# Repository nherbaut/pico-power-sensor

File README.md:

# PicoPower hand-soldered prototype

Two prototype boards for measuring voltage, current, power and energy consumed by a Raspberry Pi during AI tasks. This is the **proto branch**, with its own hand-solderable design and project history.

The interposer carries bench-supply protection and a 5 mΩ shunt. A separately USB-powered Pico carrier reads the INA228 monitor, logs measurements to microSD and drives programmable indicators.

## Current documentation

- [Requirements](docs/requirements.md) and [architecture](docs/architecture.md)
- [Bill of materials](hardware/bom.csv) and [purchase list](hardware/purchase-bom.csv)
- [Release checklist](hardware/release-checklist.csv)
- [Interposer layout](docs/interposer-layout.md) and [carrier layout](docs/carrier-layout.md)
- [Assembly and circuit explanation](docs/how-it-works.md)
- [Project handoff](HANDOFF.md) and [working instructions](AGENTS.md)

The hardware is **not released for fabrication or connection to a Pi**. Calculated values and automated checks are not bench measurements. The [2026-11-02 BOM review](docs/bom-audit-2026-11-02.md) records procurement gaps and package minimums. A [32 GB measurement-storage card](docs/measurement-storage-card.md) has been selected for prototype qualification. No parts have been purchased, as confirmed by the owner.

## Website

GitHub Pages publishes this branch. The workflow always checks out `proto`, including manual runs. Documentation and CSV tables are generated from this branch's source files; linked design files and evidence are available as downloads.

Run `make site-check BASE_URL=https://nherbaut.github.io/pico-power-sensor/` to build the site and check internal links. Hugo is required. Run `make site-serve` for a local preview.

## Hardware editing

Follow the regeneration instructions in [HANDOFF.md](HANDOFF.md). Hardware generators live in `hardware/kicad/`; the website build never regenerates or changes the CAD.

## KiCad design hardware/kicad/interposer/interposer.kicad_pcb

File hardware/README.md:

# Hardware

Start with [understanding the two boards](../docs/pcb-guide.md) for a plain-language explanation of the components, assembly and remaining work.

The [BOM](bom.csv) represents a proposed instrument, not a purchase record. [Procurement](procurement.csv) and [inventory](inventory.csv) start empty. Sources and review obligations are recorded with each component.

The first instrument combines the [custom interposer](pcb/interposer/README.md) and a Pico 2 W on the [carrier](pcb/carrier/README.md). The carrier adds five GPIO-controlled indicators, a JST-XH interposer connection and a microSD slot with its own USB-fed regulator. The Korad U202 supplies the DUT at the planned 5.1 V setting through a direct DC path. The card regulator belongs to the separately powered instrument, outside DUT measurements.

The replaceable fuse and shunt are mounted on the interposer. Current is sensed with a dedicated Kelvin pair. An upstream electronic switch disconnects incorrectly connected or excessive input voltage; it does not regulate output voltage. Its low-resistance power path still introduces a small voltage drop that must be checked under load.

The [optional BOM](optional-bom.csv) contains shared bench equipment. Calibration equipment is not part of the finished instrument.

Read the [current review findings and printable mock-ups](review/README.md), [passive component proposals](passive-proposals.csv) and [release checklist](release-checklist.csv). The [release procedure](../docs/release.md) separates prototype fabrication from assembled-board validation before Pi connection. Both gates remain blocked.

Current prototype work: [design review](../docs/design-review.md), [assembly sourcing](../docs/assembly-sourcing.md) and [fablab validation](../docs/fablab-validation.md).

The [electronic protection study](../docs/electronic-protection.md) compares fuse replacement and a copper alternative. Main CAD retains its cartridge design until the new control circuitry is qualified.

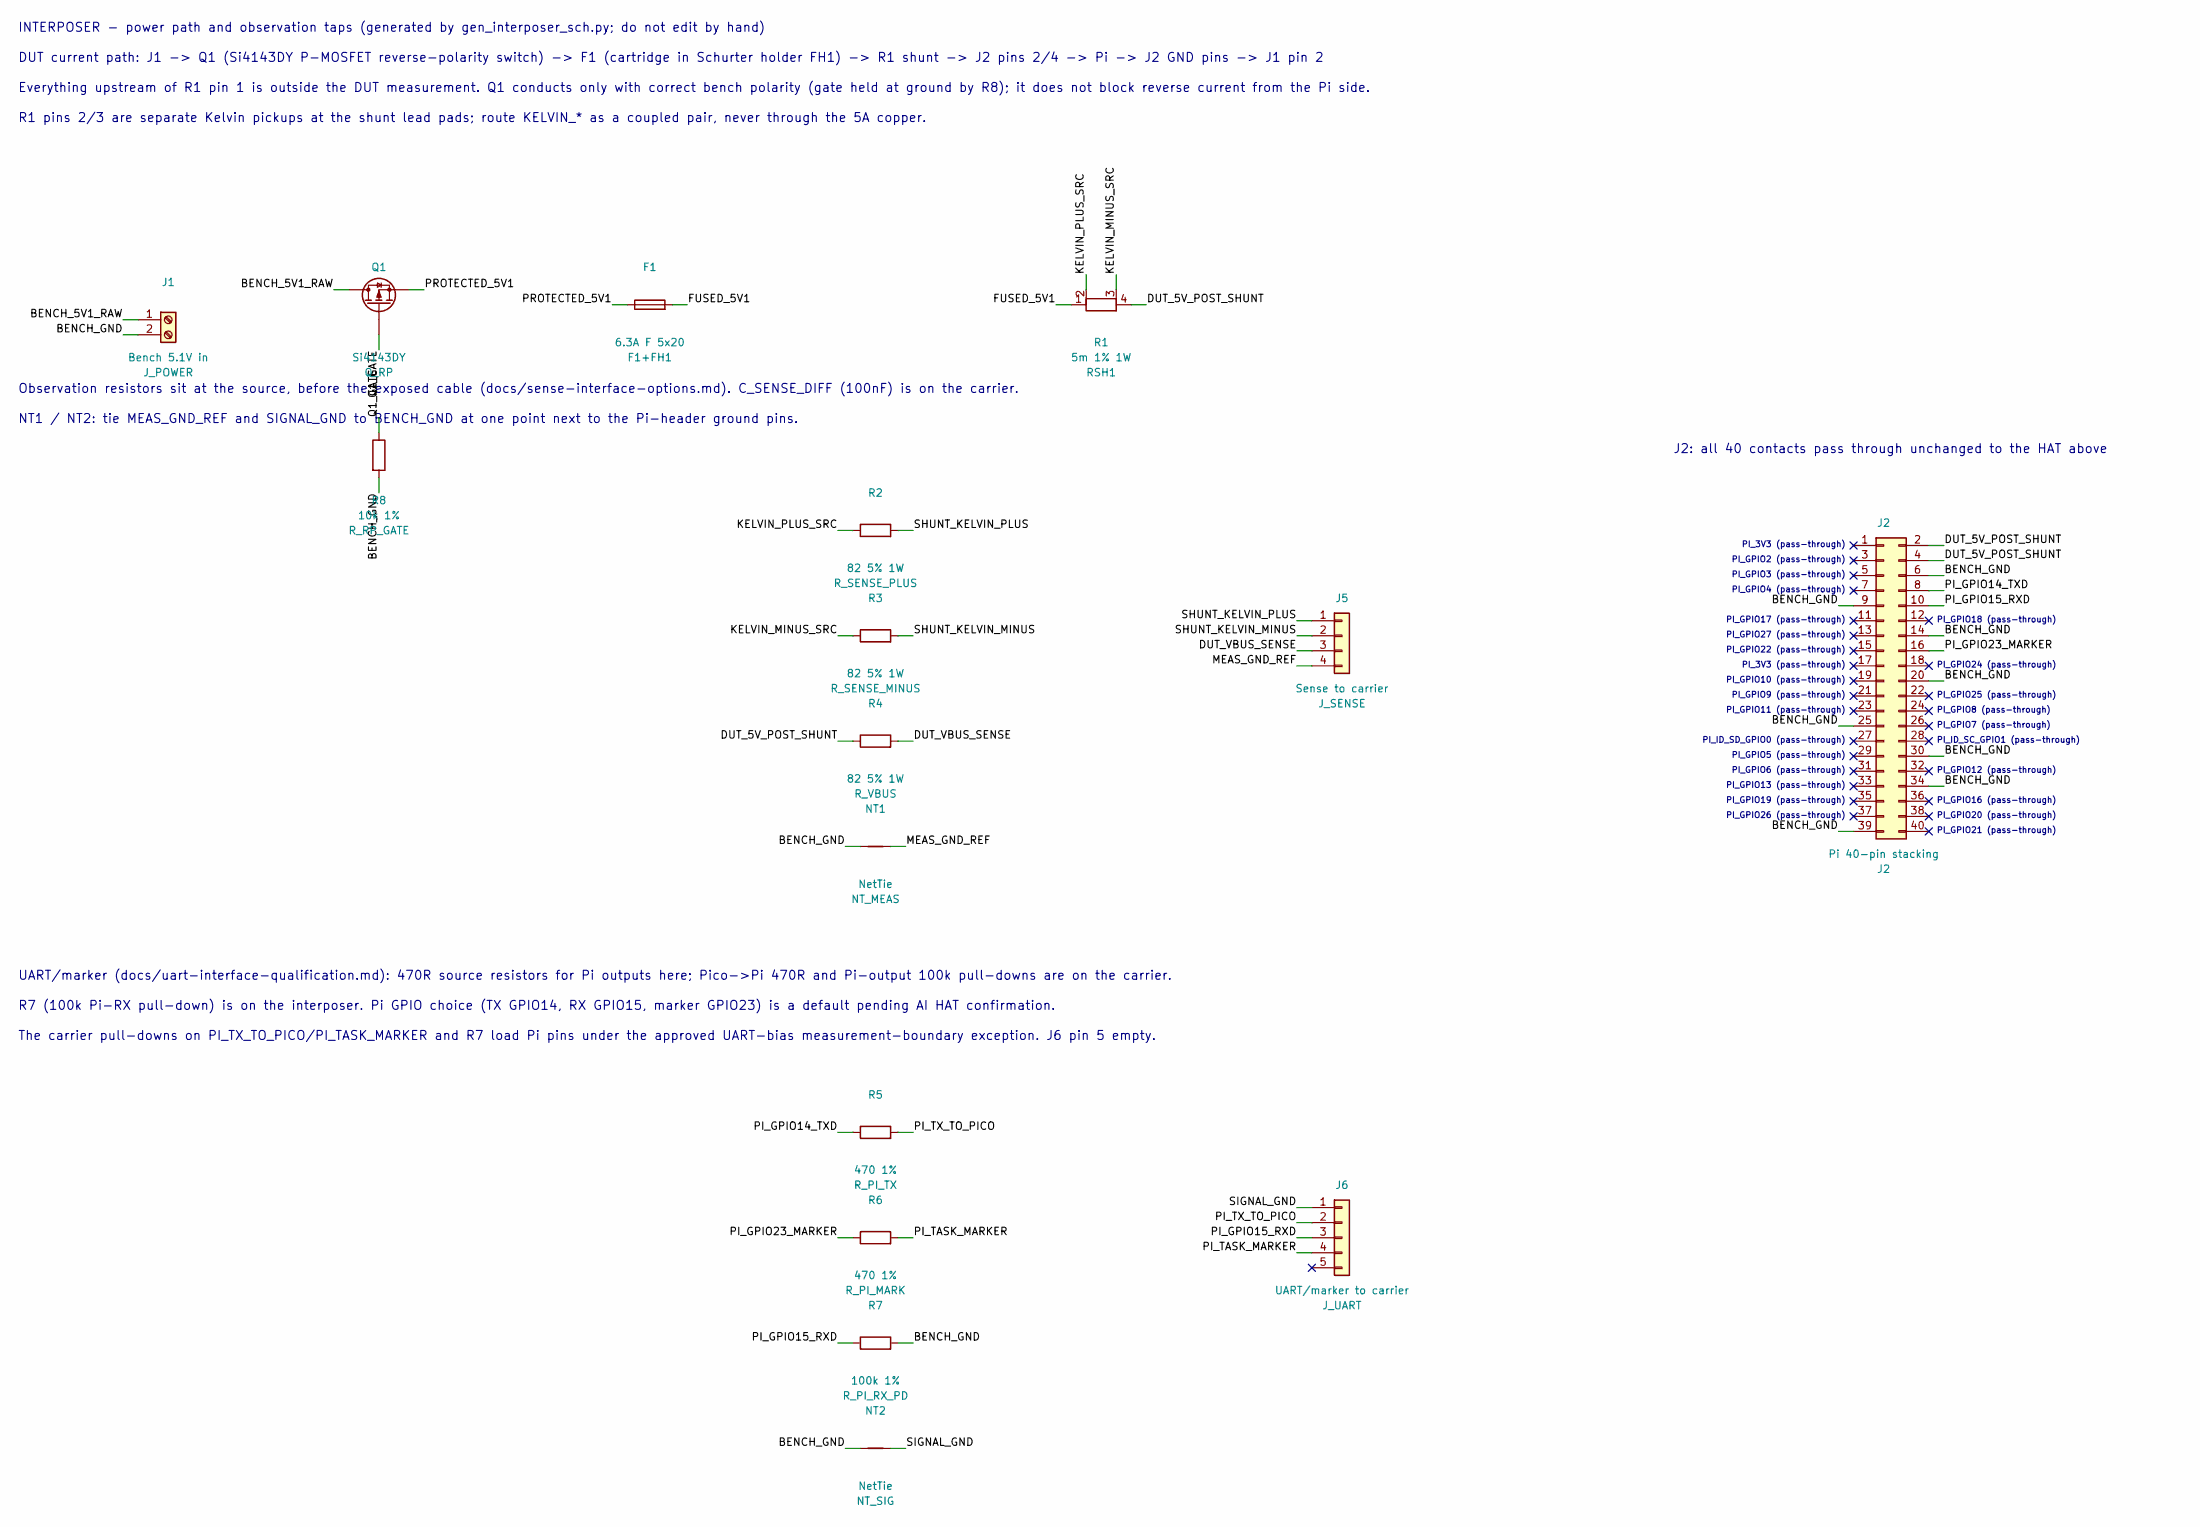
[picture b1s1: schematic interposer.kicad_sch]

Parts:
F1: 6.3A F 5x20; Fuseholder_Schurter_0031.8201_P22.5mm_D1.35mm; MPN Littelfuse 021706.3MXP in Schurter 0031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
J1: Bench 5.1V in; TerminalBlock_WE_691137710002_P5.00mm_D1.35mm; MPN Wurth Elektronik 691137710002
J2: Pi 40-pin stacking; PiStack_Adafruit2223_2x20_P2.54mm_D1.10mm; MPN Adafruit 2223 (square-pin)
J5: Sense to carrier; JST_XH_B4B-XH-A_1x04_P2.50mm_Vertical_1.8mm; MPN JST B4B-XH-A
J6: UART/marker to carrier; JST_XH_B5B-XH-A_1x05_P2.50mm_Vertical_1.8mm; MPN JST B5B-XH-A
NT1, NT2: NetTie; NetTie-2_SMD_Pad0.5mm
Q1: Si4143DY; SOIC-8_3.9x4.9mm_P1.27mm_SSSGDDDD; MPN Vishay Si4143DY-T1-GE3 (SO-8: pins 1-3 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
R1: 5m 1% 1W; R_Shunt_Bourns_MSR1_P11.40mm_Kelvin; MPN Bourns MSR1-0R005F1
R2, R3, R4: 82 5% 1W; R_Axial_L6.5mm_D2.5mm_P10.16mm_Horizontal_1.8mm; MPN Vishay PR01000108209JR500
R5, R6: 470 1%; R_Axial_L6.5mm_D2.5mm_P10.16mm_Horizontal_1.8mm; MPN Vishay MRS25000C4700FCT00
R7: 100k 1%; R_Axial_L6.5mm_D2.5mm_P10.16mm_Horizontal_1.8mm; MPN Vishay MRS25000C1003FCT00
R8: 10k 1%; R_Axial_L6.5mm_D2.5mm_P2.54mm_Vertical_1.8mm; MPN Vishay MRS25000C1002FCT00

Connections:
/BENCH_5V1_RAW: J1.1, Q1.D
/BENCH_GND: J1.2, J2.6, J2.9, J2.14, J2.20, J2.25, J2.30, J2.34, J2.39, NT1.1, NT2.1, R7.2, R8.2
/DUT_5V_POST_SHUNT: J2.2, J2.4, R1.4, R4.1
/DUT_VBUS_SENSE: J5.3, R4.2
/FUSED_5V1: F1.2, R1.1
/KELVIN_MINUS_SRC: R1.3, R3.1
/KELVIN_PLUS_SRC: R1.2, R2.1
/MEAS_GND_REF: J5.4, NT1.2
/PI_GPIO14_TXD: J2.8, R5.1
/PI_GPIO15_RXD: J2.10, J6.3, R7.1
/PI_GPIO23_MARKER: J2.16, R6.1
/PI_TASK_MARKER: J6.4, R6.2
/PI_TX_TO_PICO: J6.2, R5.2
/PROTECTED_5V1: F1.1, Q1.S
/Q1_GATE: Q1.G, R8.1
/SHUNT_KELVIN_MINUS: J5.2, R3.2
/SHUNT_KELVIN_PLUS: J5.1, R2.2
/SIGNAL_GND: J6.1, NT2.2

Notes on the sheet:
PI_3V3 (pass-through)
PI_GPIO17 (pass-through)
PI_GPIO18 (pass-through)
PI_GPIO27 (pass-through)
PI_GPIO22 (pass-through)
PI_GPIO24 (pass-through)
PI_GPIO10 (pass-through)
PI_GPIO9 (pass-through)
PI_GPIO25 (pass-through)
PI_GPIO11 (pass-through)
PI_GPIO8 (pass-through)
PI_GPIO7 (pass-through)
PI_ID_SD_GPIO0 (pass-through)
PI_ID_SC_GPIO1 (pass-through)
PI_GPIO5 (pass-through)
PI_GPIO2 (pass-through)
PI_GPIO6 (pass-through)
PI_GPIO12 (pass-through)
PI_GPIO13 (pass-through)
PI_GPIO19 (pass-through)
PI_GPIO16 (pass-through)
PI_GPIO26 (pass-through)
PI_GPIO20 (pass-through)
PI_GPIO21 (pass-through)
PI_GPIO3 (pass-through)
PI_GPIO4 (pass-through)
INTERPOSER - power path and observation taps (generated by gen_interposer_sch.py; do not edit by hand)
DUT current path: J1 -> Q1 (Si4143DY P-MOSFET reverse-polarity switch) -> F1 (cartridge in Schurter holder FH1) -> R1 shunt -> J2 pins 2/4 -> Pi -> J2 GND pins -> J1 pin 2
Everything upstream of R1 pin 1 is outside the DUT measurement. Q1 conducts only with correct bench polarity (gate held at ground by R8); it does not block reverse current from the Pi side.
R1 pins 2/3 are separate Kelvin pickups at the shunt lead pads; route KELVIN_* as a coupled pair, never through the 5A copper.
Observation resistors sit at the source, before the exposed cable (docs/sense-interface-options.md). C_SENSE_DIFF (100nF) is on the carrier.
NT1 / NT2: tie MEAS_GND_REF and SIGNAL_GND to BENCH_GND at one point next to the Pi-header ground pins.
UART/marker (docs/uart-interface-qualification.md): 470R source resistors for Pi outputs here; Pico->Pi 470R and Pi-output 100k pull-downs are on the carrier.
R7 (100k Pi-RX pull-down) is on the interposer. Pi GPIO choice (TX GPIO14, RX GPIO15, marker GPIO23) is a default pending AI HAT confirmation.
The carrier pull-downs on PI_TX_TO_PICO/PI_TASK_MARKER and R7 load Pi pins under the approved UART-bias measurement-boundary exception. J6 pin 5 empty.
J2: all 40 contacts pass through unchanged to the HAT above

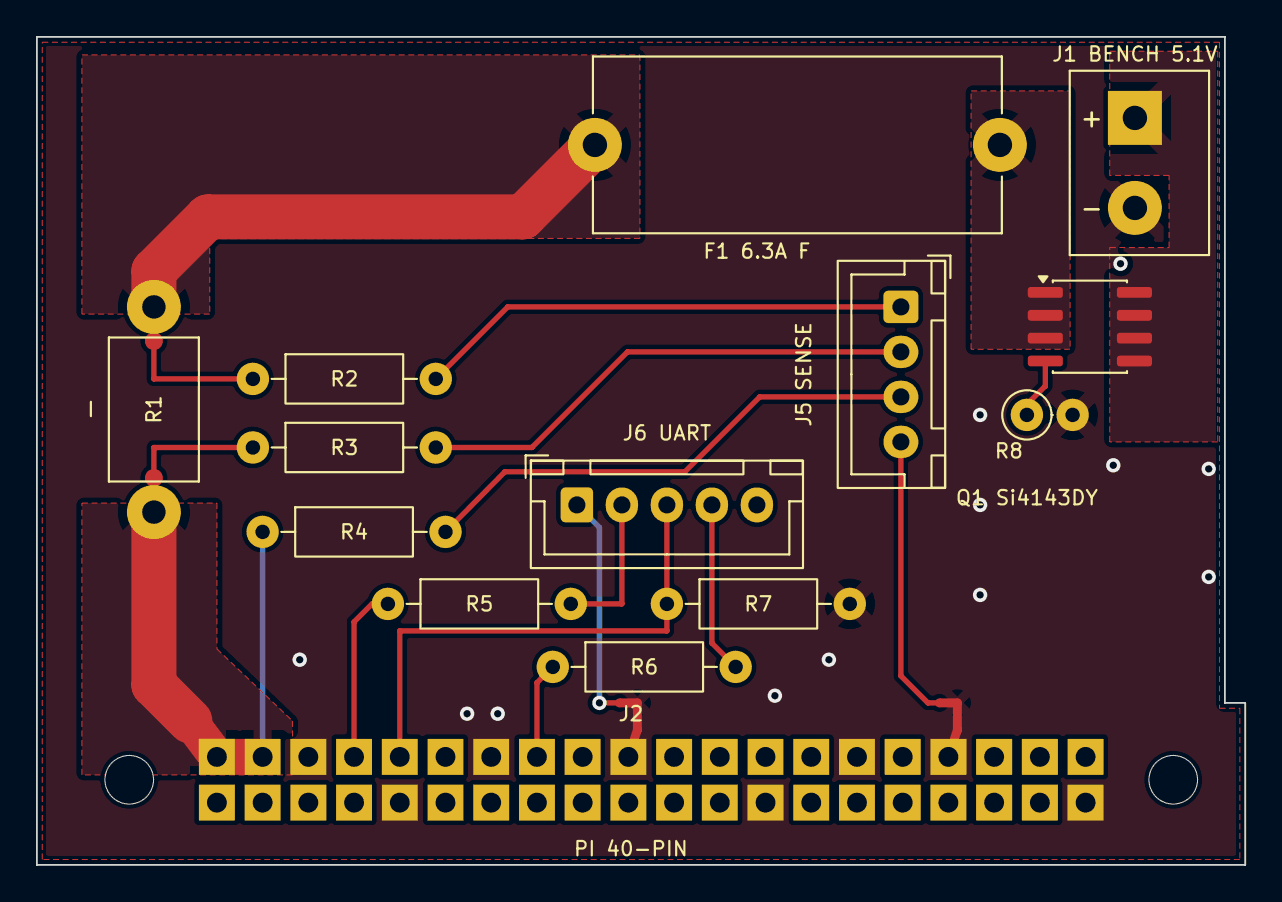
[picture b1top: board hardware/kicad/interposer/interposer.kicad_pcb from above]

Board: 2 copper layers, 67.1 x 46.0 mm, 18 parts (0 on the bottom side), 18 nets.

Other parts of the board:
H1, H2: MountingHole_2.7mm_M2.5

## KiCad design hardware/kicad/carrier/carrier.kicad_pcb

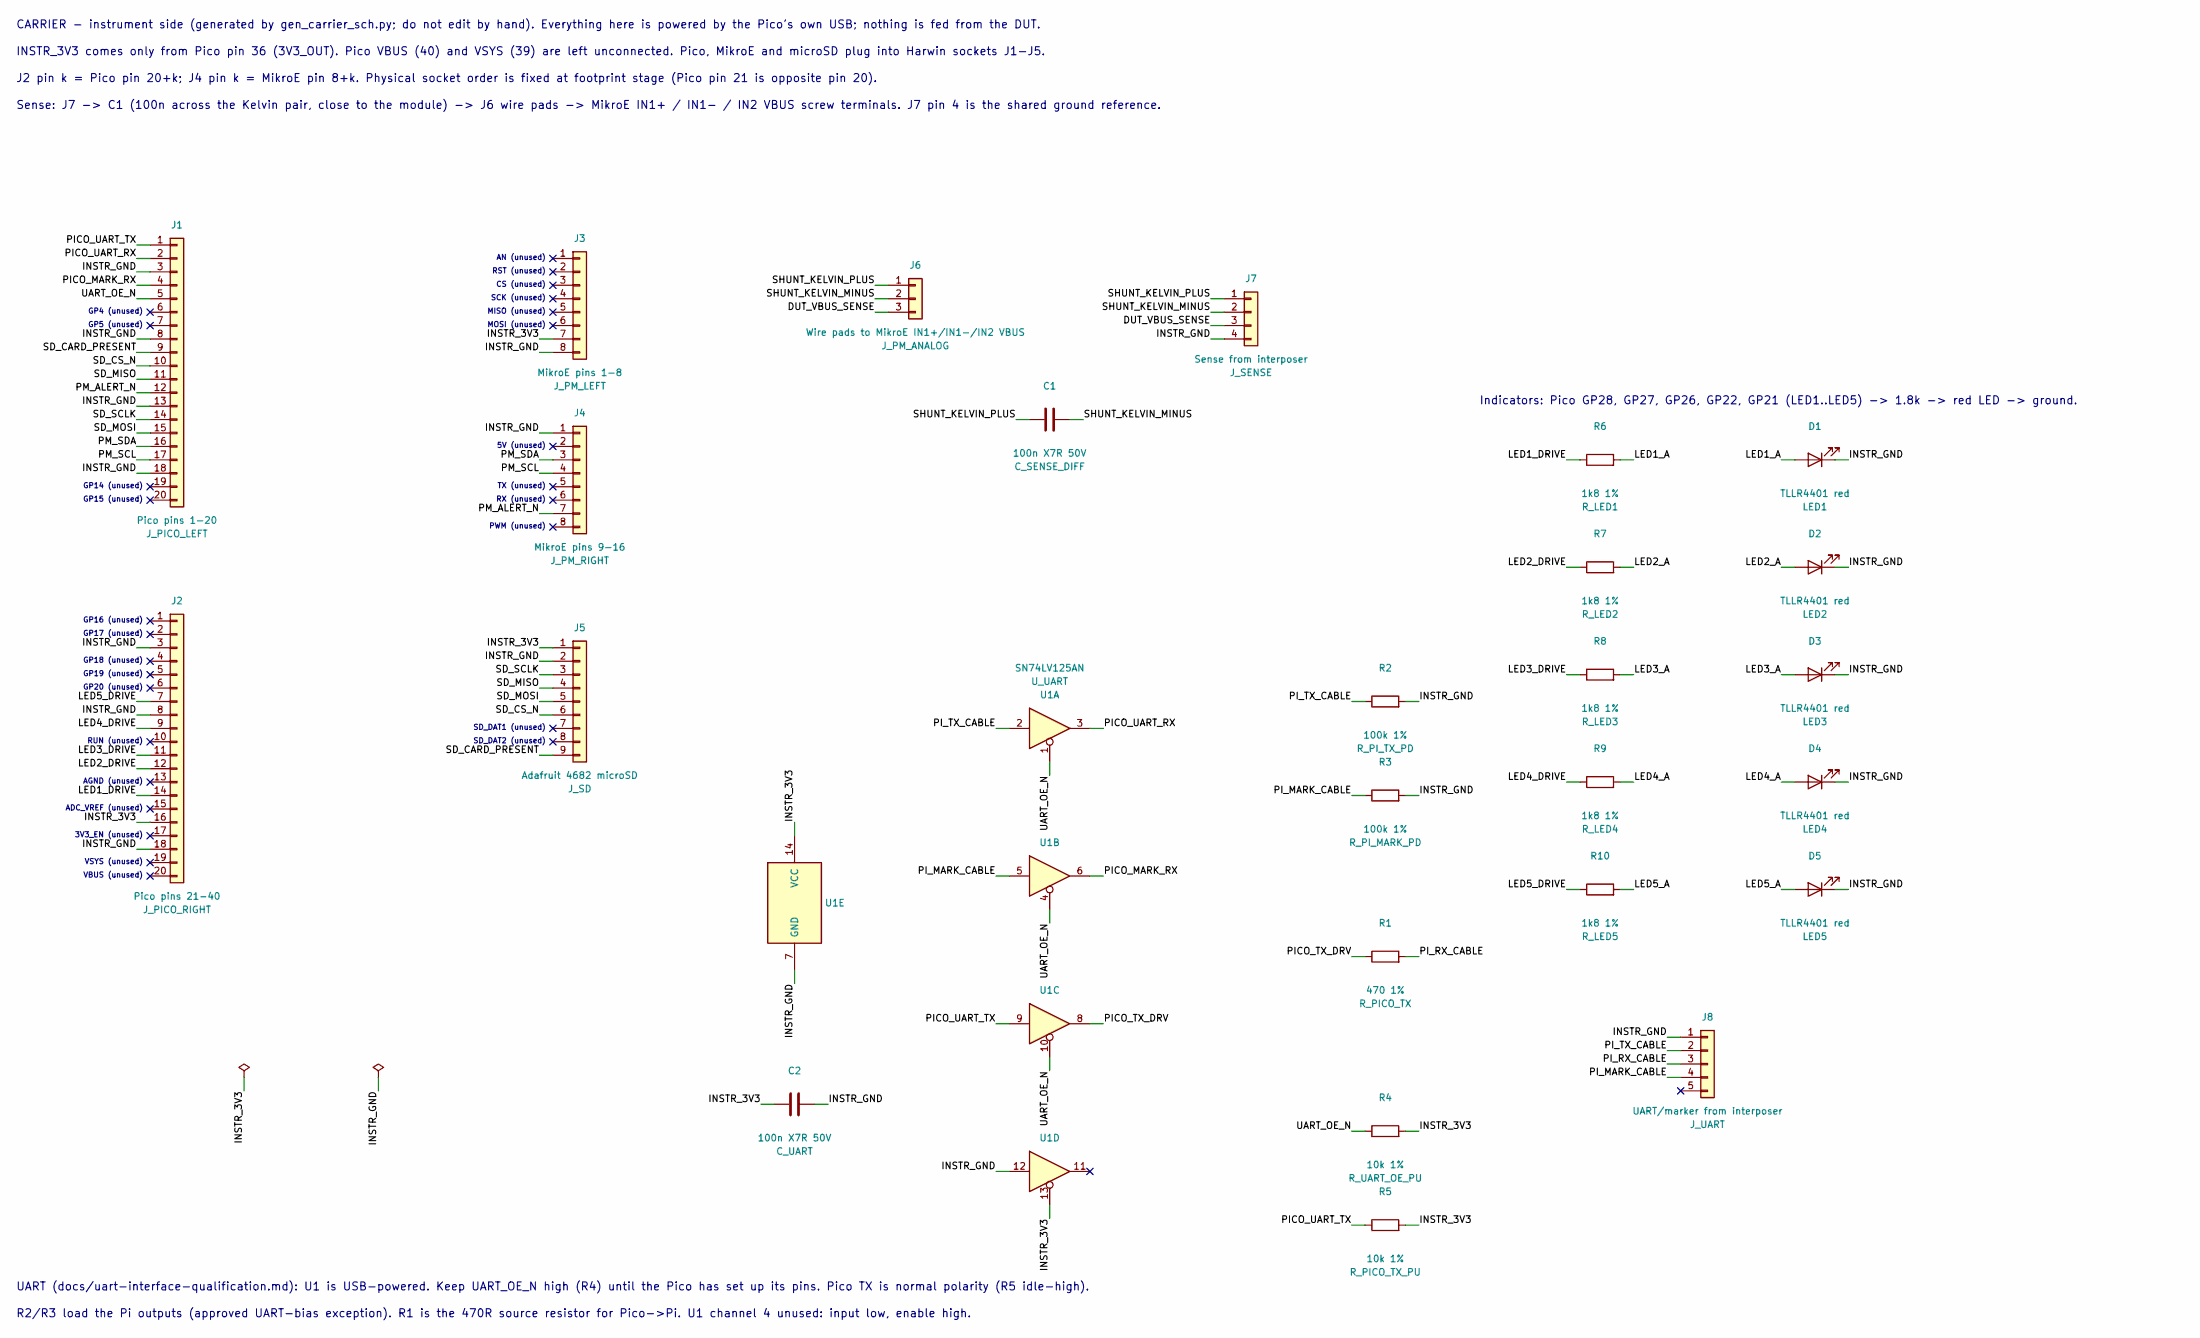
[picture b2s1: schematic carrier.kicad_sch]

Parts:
C1, C2: 100n X7R 50V; C_Radial_KEMET_C315_P2.54mm; MPN KEMET C315C104K5R5TA
D1, D2, D3, D4, D5: TLLR4401 red; LED_D3.0mm; MPN Vishay TLLR4401
J1: Pico pins 1-20; Socket_Harwin_M20-782_1x20_P2.54mm; MPN Harwin M20-7822042
J2: Pico pins 21-40; Socket_Harwin_M20-782_1x20_P2.54mm; MPN Harwin M20-7822042
J3: MikroE pins 1-8; Socket_Harwin_M20-782_1x08_P2.54mm; MPN Harwin M20-7820842
J4: MikroE pins 9-16; Socket_Harwin_M20-782_1x08_P2.54mm; MPN Harwin M20-7820842
J5: Adafruit 4682 microSD; Socket_Harwin_M20-782_1x09_P2.54mm; MPN Harwin M20-7820942
J6: Wire pads to MikroE IN1+/IN1-/IN2 VBUS; WirePads_1x03_P3.81mm_D1.0mm
J7: Sense from interposer; JST_XH_B4B-XH-A_1x04_P2.50mm_Vertical_1.8mm; MPN JST B4B-XH-A
J8: UART/marker from interposer; JST_XH_B5B-XH-A_1x05_P2.50mm_Vertical_1.8mm; MPN JST B5B-XH-A
R1: 470 1%; R_Axial_L6.5mm_D2.5mm_P2.54mm_Vertical_1.8mm; MPN Vishay MRS25000C4700FCT00
R2, R3: 100k 1%; R_Axial_L6.5mm_D2.5mm_P2.54mm_Vertical_1.8mm; MPN Vishay MRS25000C1003FCT00
R4, R5: 10k 1%; R_Axial_L6.5mm_D2.5mm_P2.54mm_Vertical_1.8mm; MPN Vishay MRS25000C1002FCT00
R6, R7, R8, R9, R10: 1k8 1%; R_Axial_L6.5mm_D2.5mm_P2.54mm_Vertical_1.8mm; MPN Vishay MRS25000C1801FCT00
U1: SN74LV125AN; DIP-14_W7.62mm_Socket_1.8mm; MPN TI SN74LV125AN in TE 1-2199298-3 socket

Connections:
/DUT_VBUS_SENSE: J6.3, J7.3
/INSTR_3V3: C2.1, J2.16, J3.7, J5.1, R4.2, R5.2, U1.13, U1.14 (VCC)
/INSTR_GND: C2.2, D1.1 (K), D2.1 (K), D3.1 (K), D4.1 (K), D5.1 (K), J1.3, J1.8, J1.13, J1.18, J2.3, J2.8, J2.18, J3.8, J4.1, J5.2, J7.4, J8.1, R2.2, R3.2, U1.7 (GND), U1.12
/LED1_A: D1.2 (A), R6.2
/LED1_DRIVE: J2.14, R6.1
/LED2_A: D2.2 (A), R7.2
/LED2_DRIVE: J2.12, R7.1
/LED3_A: D3.2 (A), R8.2
/LED3_DRIVE: J2.11, R8.1
/LED4_A: D4.2 (A), R9.2
/LED4_DRIVE: J2.9, R9.1
/LED5_A: D5.2 (A), R10.2
/LED5_DRIVE: J2.7, R10.1
/PICO_MARK_RX: J1.4, U1.6
/PICO_TX_DRV: R1.1, U1.8
/PICO_UART_RX: J1.2, U1.3
/PICO_UART_TX: J1.1, R5.1, U1.9
/PI_MARK_CABLE: J8.4, R3.1, U1.5
/PI_RX_CABLE: J8.3, R1.2
/PI_TX_CABLE: J8.2, R2.1, U1.2
/PM_ALERT_N: J1.12, J4.7
/PM_SCL: J1.17, J4.4
/PM_SDA: J1.16, J4.3
/SD_CARD_PRESENT: J1.9, J5.9
/SD_CS_N: J1.10, J5.6
/SD_MISO: J1.11, J5.4
/SD_MOSI: J1.15, J5.5
/SD_SCLK: J1.14, J5.3
/SHUNT_KELVIN_MINUS: C1.2, J6.2, J7.2
/SHUNT_KELVIN_PLUS: C1.1, J6.1, J7.1
/UART_OE_N: J1.5, R4.1, U1.1, U1.4, U1.10

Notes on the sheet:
GP14 (unused)
GP15 (unused)
GP4 (unused)
GP5 (unused)
GP16 (unused)
RUN (unused)
AGND (unused)
ADC_VREF (unused)
3V3_EN (unused)
VSYS (unused)
GP17 (unused)
VBUS (unused)
GP18 (unused)
GP19 (unused)
GP20 (unused)
AN (unused)
RST (unused)
CS (unused)
SCK (unused)
MISO (unused)
MOSI (unused)
5V (unused)
TX (unused)
RX (unused)
PWM (unused)
SD_DAT1 (unused)
SD_DAT2 (unused)
CARRIER - instrument side (generated by gen_carrier_sch.py; do not edit by hand). Everything here is powered by the Pico's own USB; nothing is fed from the DUT.
INSTR_3V3 comes only from Pico pin 36 (3V3_OUT). Pico VBUS (40) and VSYS (39) are left unconnected. Pico, MikroE and microSD plug into Harwin sockets J1-J5.
J2 pin k = Pico pin 20+k; J4 pin k = MikroE pin 8+k. Physical socket order is fixed at footprint stage (Pico pin 21 is opposite pin 20).
Sense: J7 -> C1 (100n across the Kelvin pair, close to the module) -> J6 wire pads -> MikroE IN1+ / IN1- / IN2 VBUS screw terminals. J7 pin 4 is the shared ground reference.
UART (docs/uart-interface-qualification.md): U1 is USB-powered. Keep UART_OE_N high (R4) until the Pico has set up its pins. Pico TX is normal polarity (R5 idle-high).
R2/R3 load the Pi outputs (approved UART-bias exception). R1 is the 470R source resistor for Pico->Pi. U1 channel 4 unused: input low, enable high.
Indicators: Pico GP28, GP27, GP26, GP22, GP21 (LED1..LED5) -> 1.8k -> red LED -> ground.

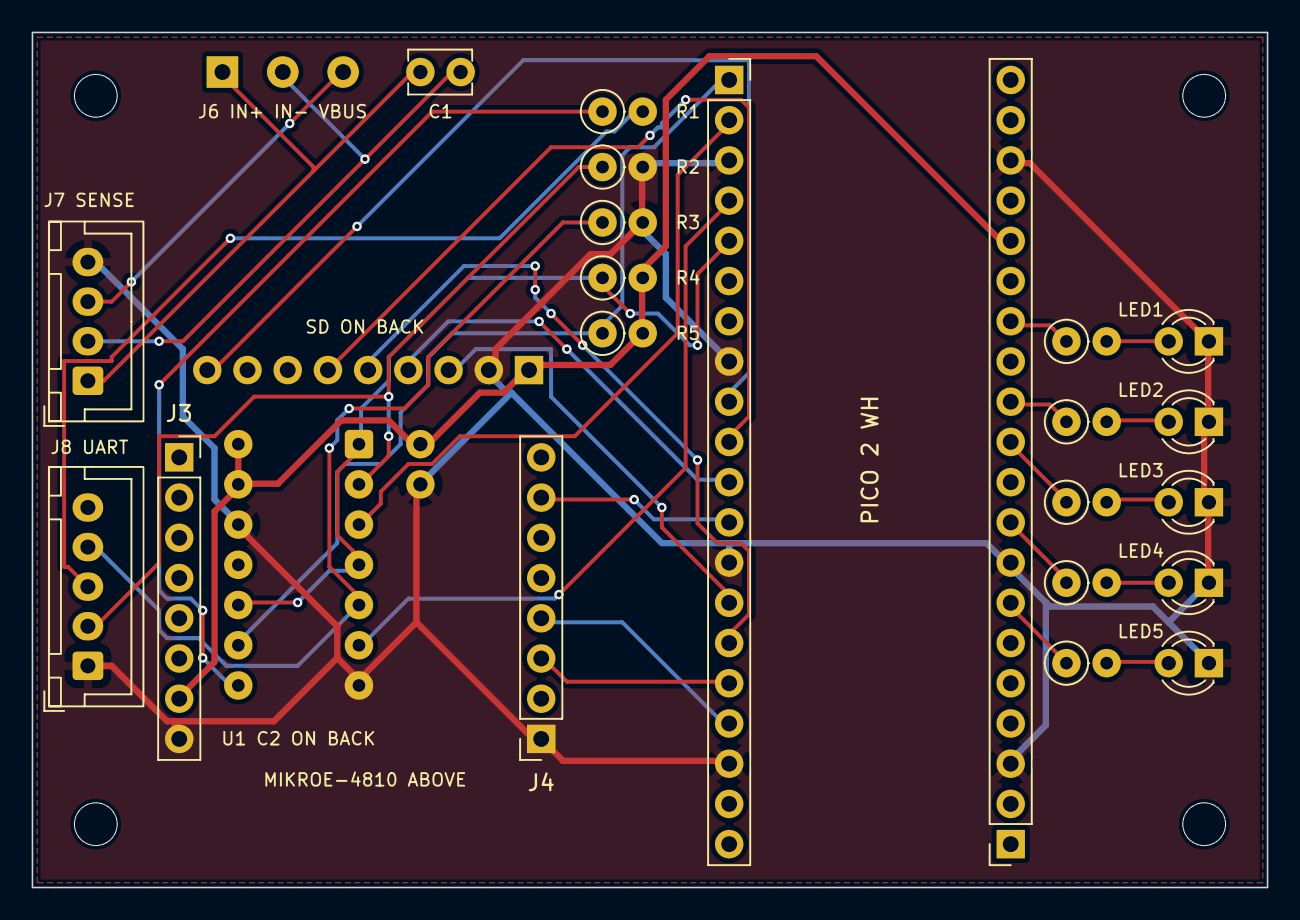
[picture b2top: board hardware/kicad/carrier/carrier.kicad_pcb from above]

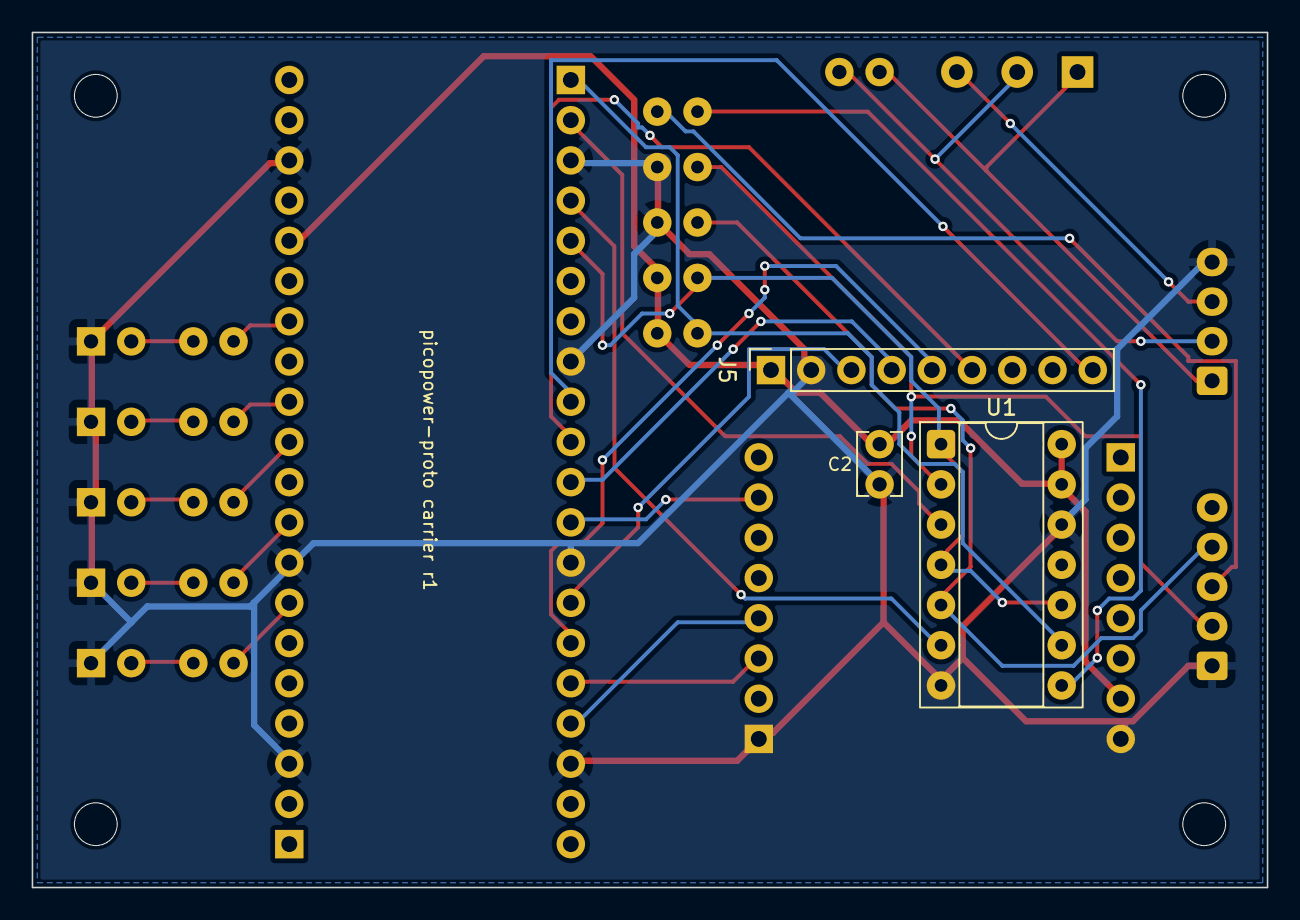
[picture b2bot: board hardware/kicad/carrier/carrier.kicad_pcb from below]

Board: 2 copper layers, 78.0 x 54.0 mm, 30 parts (3 on the bottom side), 31 nets.

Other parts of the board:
H1, H2, H3, H4: MountingHole_2.7mm_M2.5
